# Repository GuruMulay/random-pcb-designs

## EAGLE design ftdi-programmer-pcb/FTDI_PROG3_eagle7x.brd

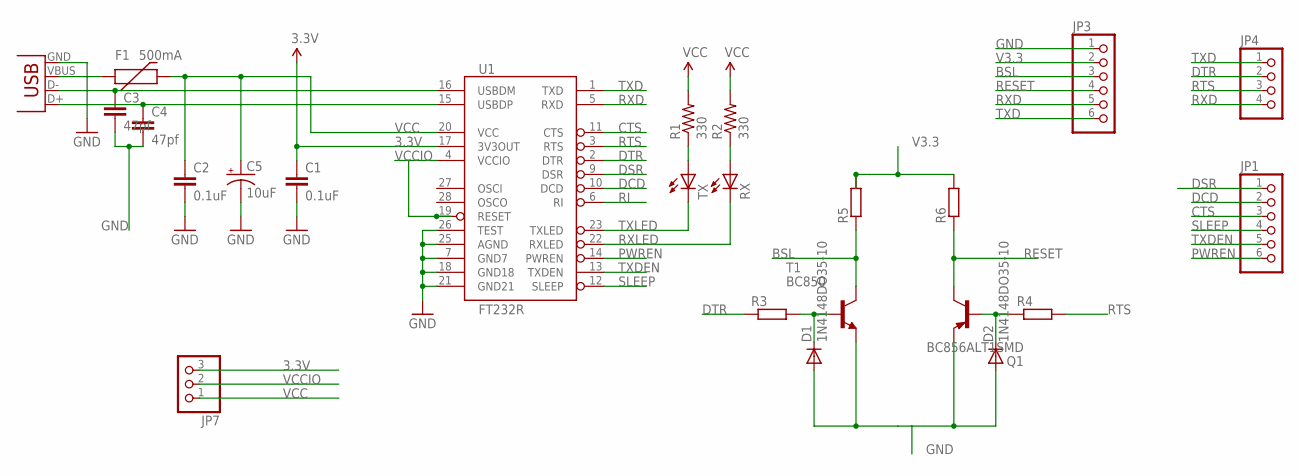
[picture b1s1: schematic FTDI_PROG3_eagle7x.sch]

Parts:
C1, C2: 0.1uF; 1206
C3: 47pf; C025-024X044
C4: 47pf; C025-025X050
C5: 10uF; CPOL-RADIAL-100UF-25V
D1, D2: 1N4148DO35-10; DO35-10
F1: 500mA; PTC-1206
JP1, JP3: PINHD-1X6; 1X06
JP4: PINHD-1X4; 1X04
JP7: PINHD-1X3; 1X03
Q1: BC856ALT1SMD; SOT23-BEC
R1, R2: 330; 1206
R3, R4, R5, R6: R-EU_0207/10; 0207/10
RX: LED1206; LED-1206
T1: BC850; SOT23
TX: LED1206; LED-1206
U1: FT232R; SSOP28DB
X2: USBPTH; USB-B-PTH

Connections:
3.3V: C1.1, JP7.3, U1.17 (3V3OUT)
BSL: JP3.3, R5.1, T1.3 (C)
CTS: JP1.3, U1.11 (CTS)
DCD: JP1.2, U1.10 (DCD)
DSR: JP1.1, U1.9 (DSR)
DTR: JP4.2, R3.1, U1.2 (DTR)
GND: C1.2, C2.2, C3.2, C4.2, C5.2 (-), D1.A, D2.A, JP3.1, Q1.E, T1.2 (E), U1.7 (GND7), U1.18 (GND18), U1.21 (GND21), U1.25 (AGND), U1.26 (TEST), X2.GND
unnamed: R1.1, TX.A
unnamed: R2.1, RX.A
unnamed: F1.1, X2.VBUS
unnamed: D1.C, R3.2, T1.1 (B)
unnamed: D2.C, Q1.B, R4.1
PWREN: JP1.6, U1.14 (PWREN)
RESET: JP3.4, Q1.C, R6.1
RI: U1.6 (RI)
RTS: JP4.3, R4.2, U1.3 (RTS)
RXD: JP3.5, JP4.4, U1.5 (RXD)
RXLED: RX.C, U1.22 (RXLED)
SLEEP: JP1.4, U1.12 (SLEEP)
TXD: JP3.6, JP4.1, U1.1 (TXD)
TXDEN: JP1.5, U1.13 (TXDEN)
TXLED: TX.C, U1.23 (TXLED)
USB_D+: C4.1, U1.15 (USBDP), X2.D+
USB_D-: C3.1, U1.16 (USBDM), X2.D-
V3.3: JP3.2, R5.2, R6.2
VCC: C2.1, C5.1 (+), F1.2, JP7.1, R1.2, R2.2, U1.20 (VCC)
VCCIO: JP7.2, U1.4 (VCCIO), U1.19 (RESET)

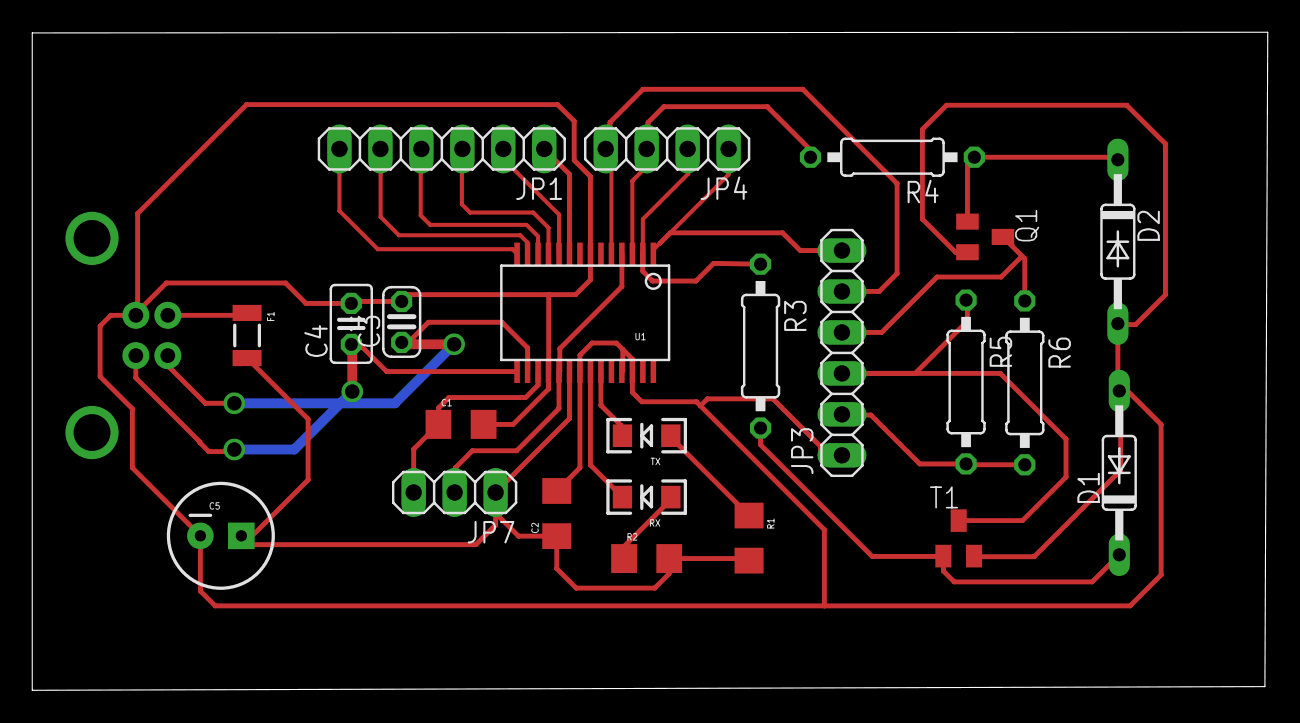
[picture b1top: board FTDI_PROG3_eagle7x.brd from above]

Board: 2 copper layers, 76.6 x 40.8 mm, 24 parts (1 on the bottom side), 26 nets.

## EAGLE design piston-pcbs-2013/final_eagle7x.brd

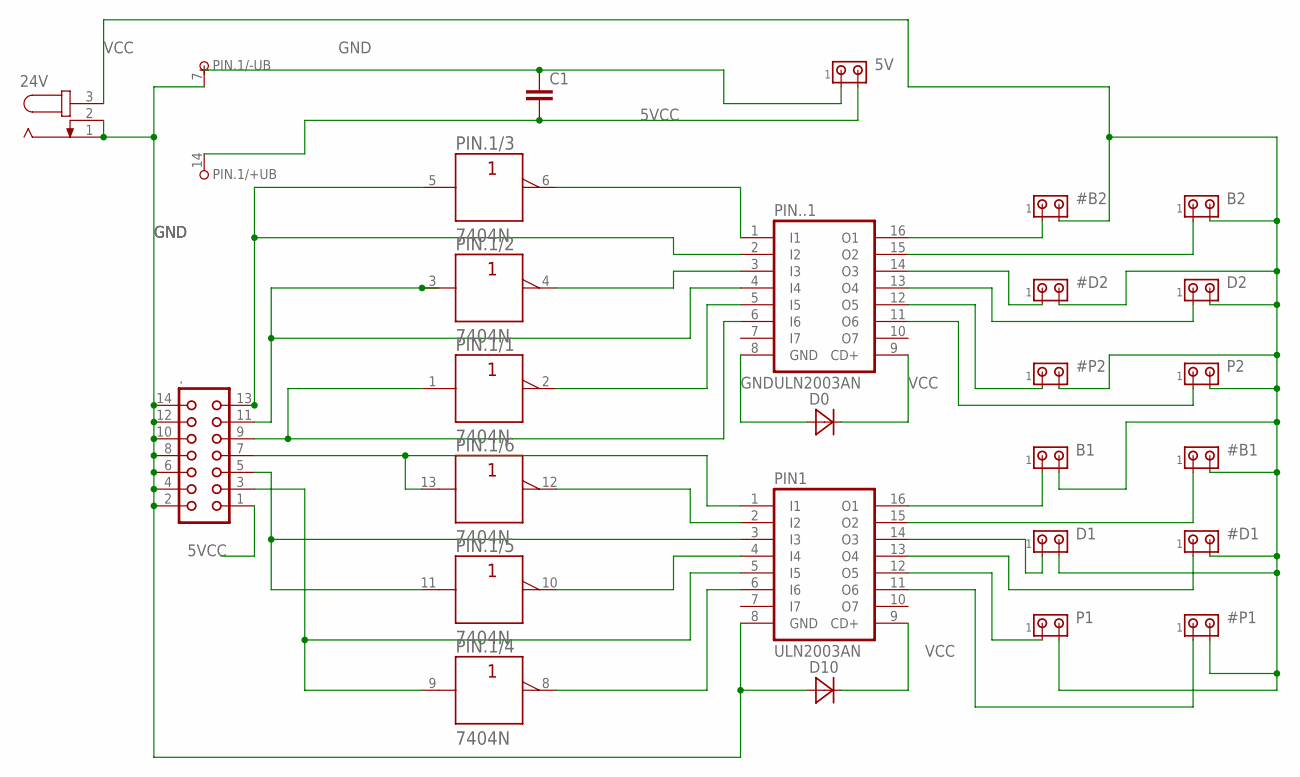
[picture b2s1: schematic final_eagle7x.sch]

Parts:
5V: MTA02-100; 10X02MTA
24V: JACK-PLUG1; SPC4078
#B1, #B2: MTA02-100; 10X02MTA
#D1, #D2: MTA02-100; 10X02MTA
#P1, #P2: MTA02-100; 10X02MTA
.: CON14
B1, B2: MTA02-100; 10X02MTA
C1: C-EUC0603; C0603
D0, D10: MBRA340T3; SMA
D1, D2: MTA02-100; 10X02MTA
P1, P2: MTA02-100; 10X02MTA
PIN1, PIN..1: ULN2003AN; DIL16
PIN.1: 7404N; DIL14

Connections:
5VCC: 5V.2, ..1, C1.2, PIN.1.14 (+UB)
GND: 5V.1, 24V.1, 24V.2, ..2, ..4, ..6, ..8, ..10, ..12, ..14, C1.1, D0.A, D10.A, PIN1.8 (GND), PIN.1.7 (-UB), PIN..1.8 (GND)
unnamed: PIN.1.4 (Y), PIN..1.3 (I3)
unnamed: PIN.1.2 (Y), PIN..1.5 (I5)
unnamed: ..13, PIN.1.5 (A), PIN..1.2 (I2)
unnamed: ..7, PIN1.1 (I1), PIN.1.13 (A)
unnamed: ..11, PIN.1.3 (A), PIN..1.4 (I4)
unnamed: PIN.1.6 (Y), PIN..1.1 (I1)
unnamed: ..9, PIN.1.1 (A), PIN..1.6 (I6)
unnamed: ..5, PIN1.3 (I3), PIN.1.11 (A)
unnamed: ..3, PIN1.5 (I5), PIN.1.9 (A)
unnamed: PIN1.2 (I2), PIN.1.12 (Y)
unnamed: PIN1.4 (I4), PIN.1.10 (Y)
unnamed: PIN1.6 (I6), PIN.1.8 (Y)
unnamed: #B2.1, PIN..1.16 (O1)
unnamed: B2.1, PIN..1.15 (O2)
unnamed: #D2.1, PIN..1.14 (O3)
unnamed: D2.1, PIN..1.13 (O4)
unnamed: #P2.1, PIN..1.12 (O5)
unnamed: P2.1, PIN..1.11 (O6)
unnamed: B1.1, PIN1.16 (O1)
unnamed: D1.1, PIN1.14 (O3)
unnamed: #D1.1, PIN1.13 (O4)
unnamed: P1.1, PIN1.12 (O5)
unnamed: #P1.1, PIN1.11 (O6)
unnamed: #B1.1, PIN1.15 (O2)
VCC: 24V.3, #B1.2, #B2.2, #D1.2, #D2.2, #P1.2, #P2.2, B1.2, B2.2, D0.C, D1.2, D2.2, D10.C, P1.2, P2.2, PIN1.9 (CD+), PIN..1.9 (CD+)

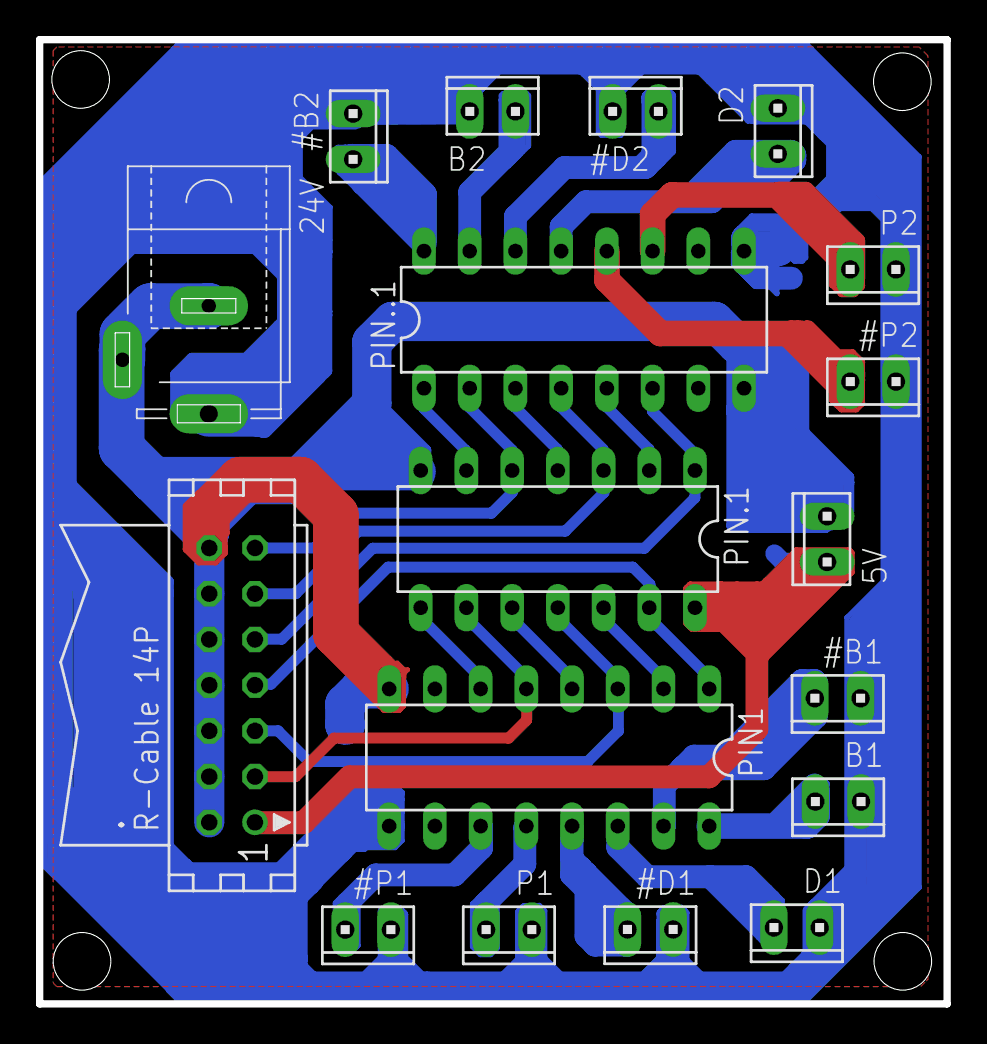
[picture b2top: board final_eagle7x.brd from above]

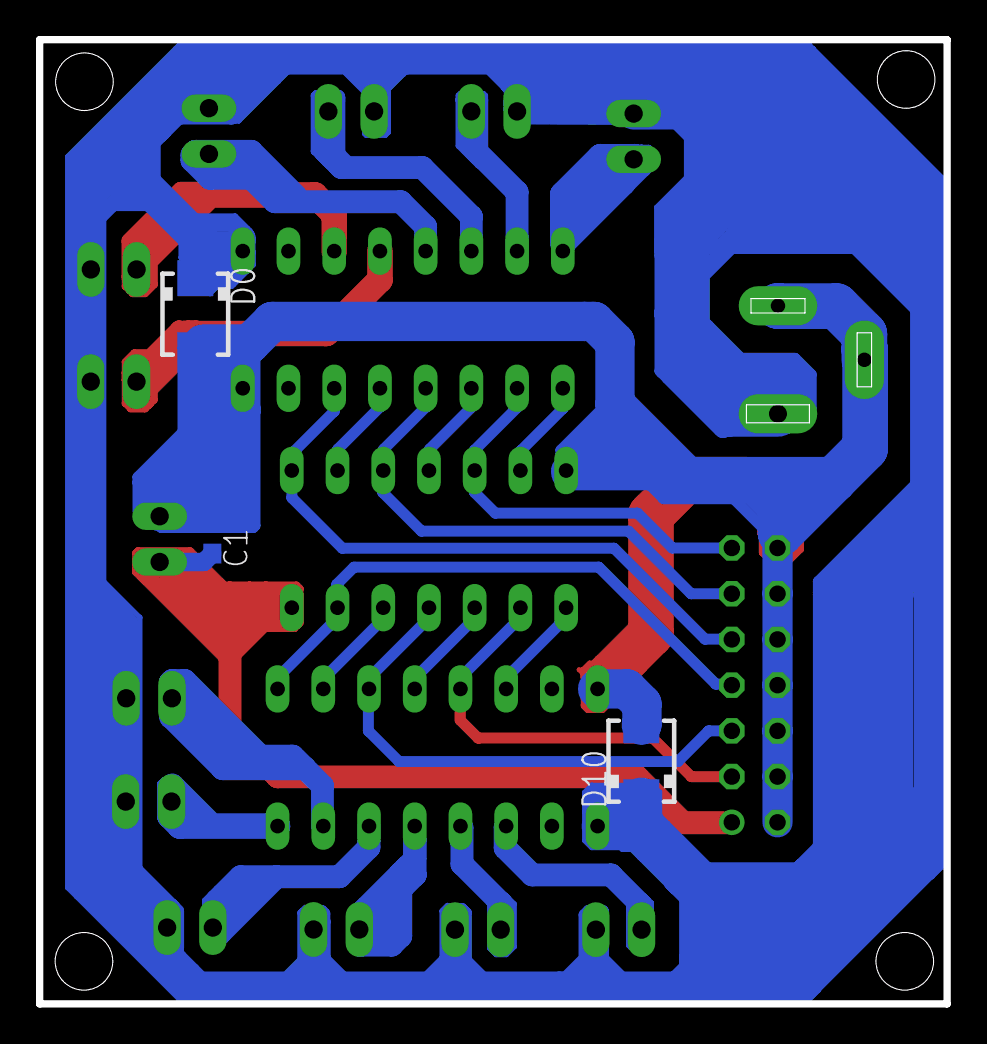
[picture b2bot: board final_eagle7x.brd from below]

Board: 2 copper layers, 50.4 x 53.6 mm, 21 parts (3 on the bottom side), 27 nets.
